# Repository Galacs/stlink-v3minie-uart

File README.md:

# STLINK-V3 MINIE UART

UART adapter for the stlink v3 minie

## Top preview

## Preview 3d render

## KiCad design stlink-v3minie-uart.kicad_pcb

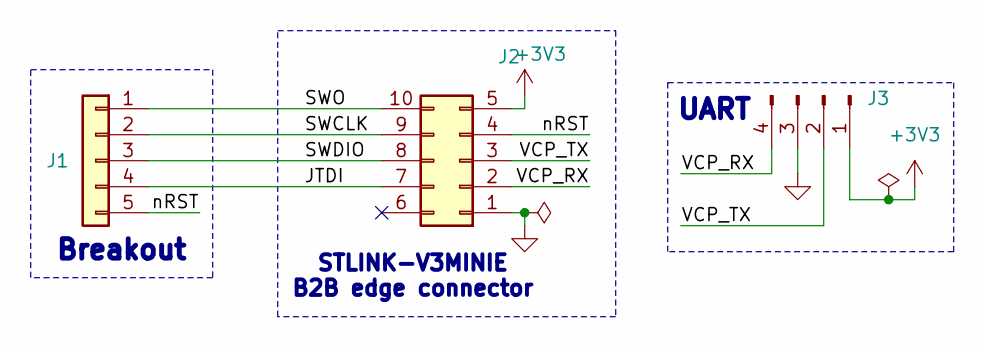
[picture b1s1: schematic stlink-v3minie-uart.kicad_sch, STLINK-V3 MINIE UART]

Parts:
J1: Conn_01x05; PinHeader_1x05_P2.54mm_Vertical
J2: Conn_02x05_Top_Bottom; KYOCERA_AVX9159-006
J3: Conn_01x04_Pin; PinHeader_1x04_P2.54mm_Horizontal

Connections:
+3V3: J2.5, J3.1
/JTDI: J1.4, J2.7
/SWCLK: J1.2, J2.9
/SWDIO: J1.3, J2.8
/SWO: J1.1, J2.10
/VCP_RX: J2.2, J3.4
/VCP_TX: J2.3, J3.2
/nRST: J1.5, J2.4
GND: J2.1, J3.3

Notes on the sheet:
Breakout
STLINK-V3MINIE B2B edge connector
UART

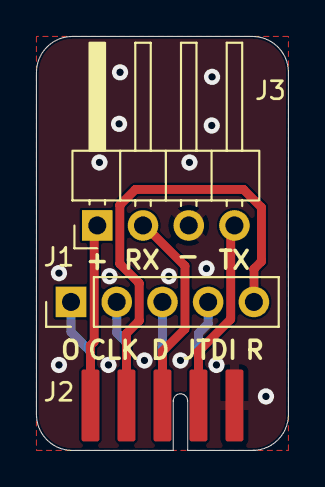
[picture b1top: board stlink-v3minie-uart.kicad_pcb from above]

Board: 2 copper layers, 14.0 x 23.0 mm, 3 parts (0 on the bottom side), 9 nets.

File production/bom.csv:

Designator,Footprint,Quantity,Value,LCSC Part #
J1,PinHeader_1x05_P2.54mm_Vertical,1,Conn_01x05,
J2,KYOCERA_AVX9159-006,1,Conn_02x05_Top_Bottom,

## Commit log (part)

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2026-06-25 schem: add all connectors
2026-06-25 schem: add net classes
2026-06-25 schem: assign footprints
2026-06-25 schem: renumber
2026-06-25 schem: add title
2026-06-25 pcb: import jlc 2 layer stackup
2026-06-25 pcb: import footprints from schem
2026-06-25 pcb: initial rough placement
2026-06-25 pcb: oui
2026-06-25 pcb: add drill/place origin
2026-06-25 pcb: route and add stitching vias
2026-06-25 pcb(silk): add usr txt
2026-06-25 pcb: add title
2026-06-25 pcb(silk): add jlcjlcjlc
2026-06-25 generate production files
